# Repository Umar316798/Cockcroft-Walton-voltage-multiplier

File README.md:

# Cockcroft-Walton Voltage Multiplier PCB

A voltage multiplier circuit designed in **KiCad 9.0**. This design uses a cascading diode-capacitor ladder network to rectify an input AC or pulsed waveform into a high-voltage DC output.

<p align="center">

  <br>
  <i>Figure 1: Completed 3D Assembly Render showing SMD Component Array</i>
</p>

---

## 🛠️ System Overview & Design Layout

The hardware features symmetrical placement to reduce current inductance while maximizing trace space distance between high potential differences.

<p align="center">

  <br>
  <i>Figure 2: Complete Design Walkthrough — Electrical Schematic and Track Layout Routing </i>
</p>

### 🔧 Component Specifications
* **EDA Tool Version:** KiCad v9.0.0+
* **Layer Count:** 2-Layer Board 
* **Diodes (D1–D6):** 6x 1N4148 High-Speed Switching Diodes (SOD-123 Package)
* **Capacitors (C1–C6):** 6x 10µF Ceramic Capacitors (1206 Package)
* **Resistors (R1, R2):** 2x 1kΩ High-Power Resistors (2010 Package)

---

## 🚀 How It Works

1. **The Ladder Cascade:** Input voltage pulses charges along the capacitor ladder. Diodes act as electrical charge peak values stage-by-stage.
2. **SMD Footprint Optimization:** By replacing classic through-hole parts with low-profile **SOD-123** and **1206** footprints, parasitical inductance is nearly eliminated.
3. **Safety Isolation:** **R1** and **R2** function as surge limiting protection variables, isolating input nodes from downstream high-voltage storage banks.

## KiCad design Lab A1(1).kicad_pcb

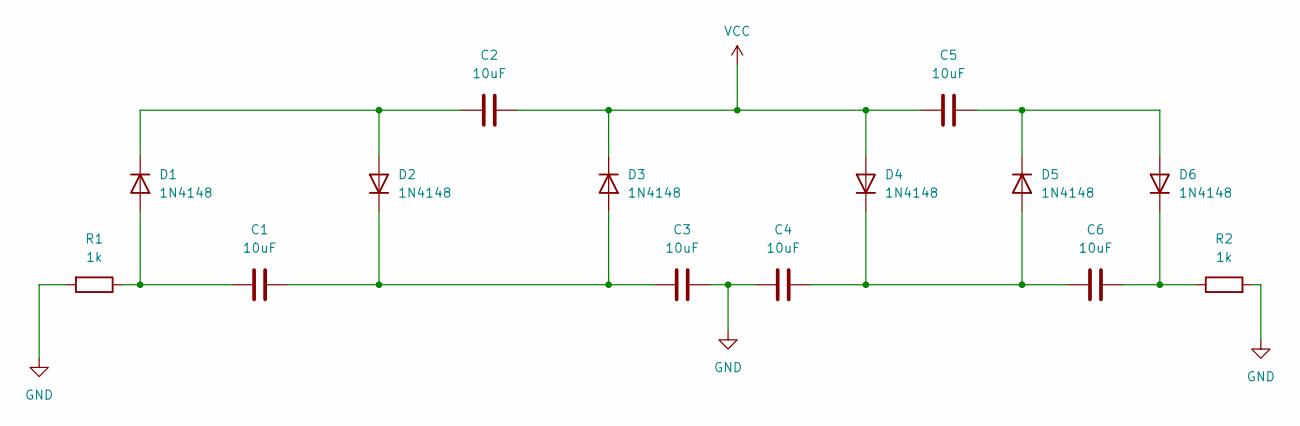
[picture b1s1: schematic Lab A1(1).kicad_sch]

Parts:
C1, C2, C3, C4, C5, C6: 10uF; C_1206_3216Metric
D1, D2, D3, D4, D5, D6: 1N4148; D_SOD-123
R1, R2: 1k; R_2010_5025Metric

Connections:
GND: C3.2, C4.1, R1.2, R2.2
unnamed: C1.1, D1.2 (A), R1.1
unnamed: C2.1, D1.1 (K), D2.2 (A)
unnamed: C1.2, C3.1, D2.1 (K), D3.2 (A)
unnamed: C4.2, C6.1, D4.1 (K), D5.2 (A)
unnamed: C5.2, D5.1 (K), D6.2 (A)
unnamed: C6.2, D6.1 (K), R2.1
VCC: C2.2, C5.1, D3.1 (K), D4.2 (A)

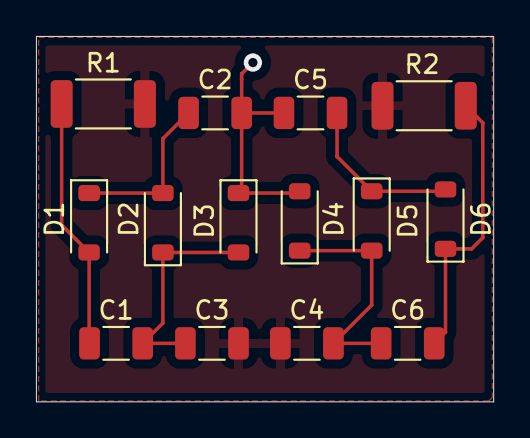
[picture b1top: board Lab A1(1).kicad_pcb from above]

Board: 2 copper layers, 25.4 x 20.3 mm, 14 parts (0 on the bottom side), 8 nets.
